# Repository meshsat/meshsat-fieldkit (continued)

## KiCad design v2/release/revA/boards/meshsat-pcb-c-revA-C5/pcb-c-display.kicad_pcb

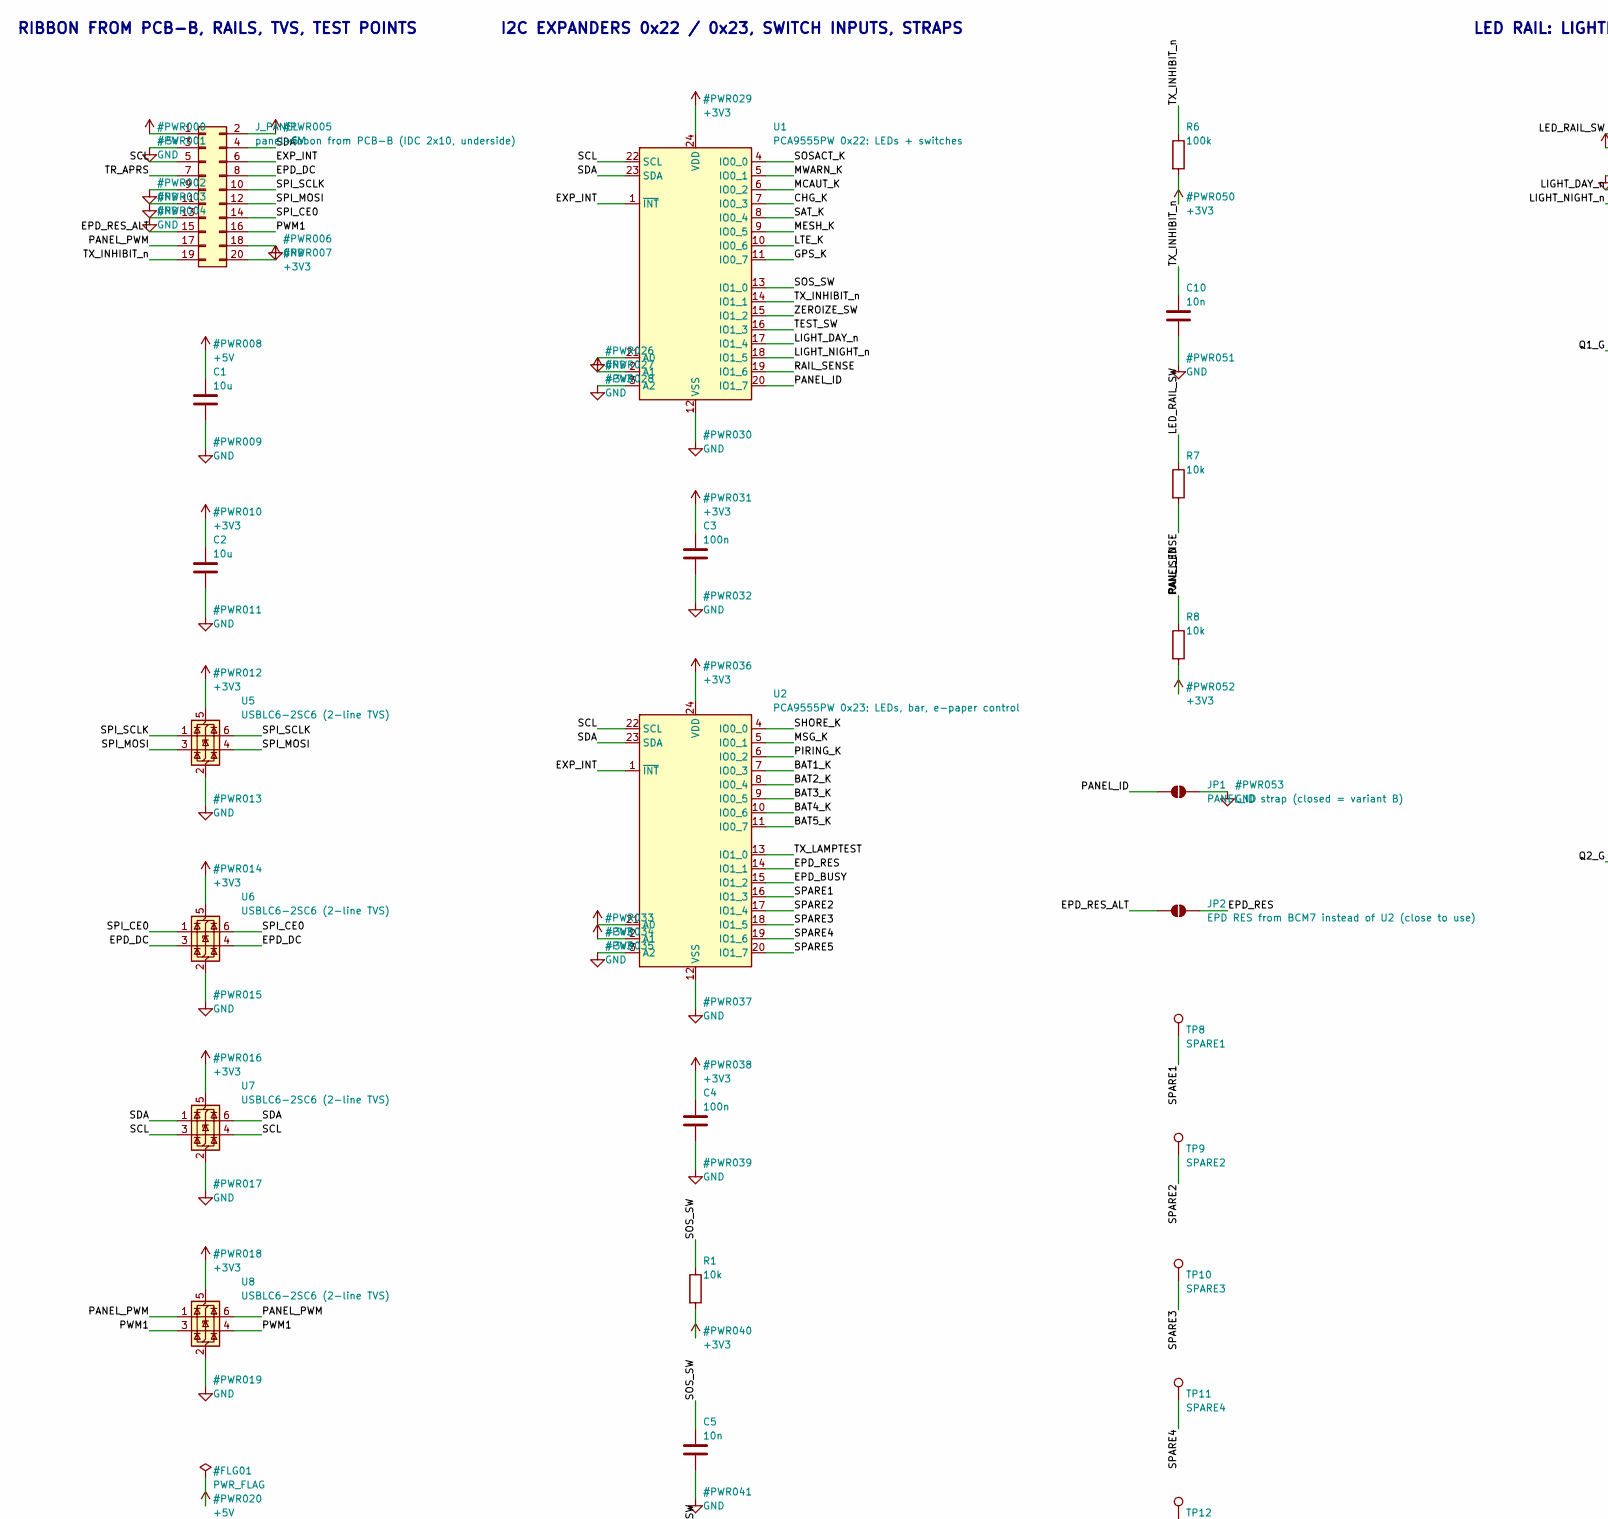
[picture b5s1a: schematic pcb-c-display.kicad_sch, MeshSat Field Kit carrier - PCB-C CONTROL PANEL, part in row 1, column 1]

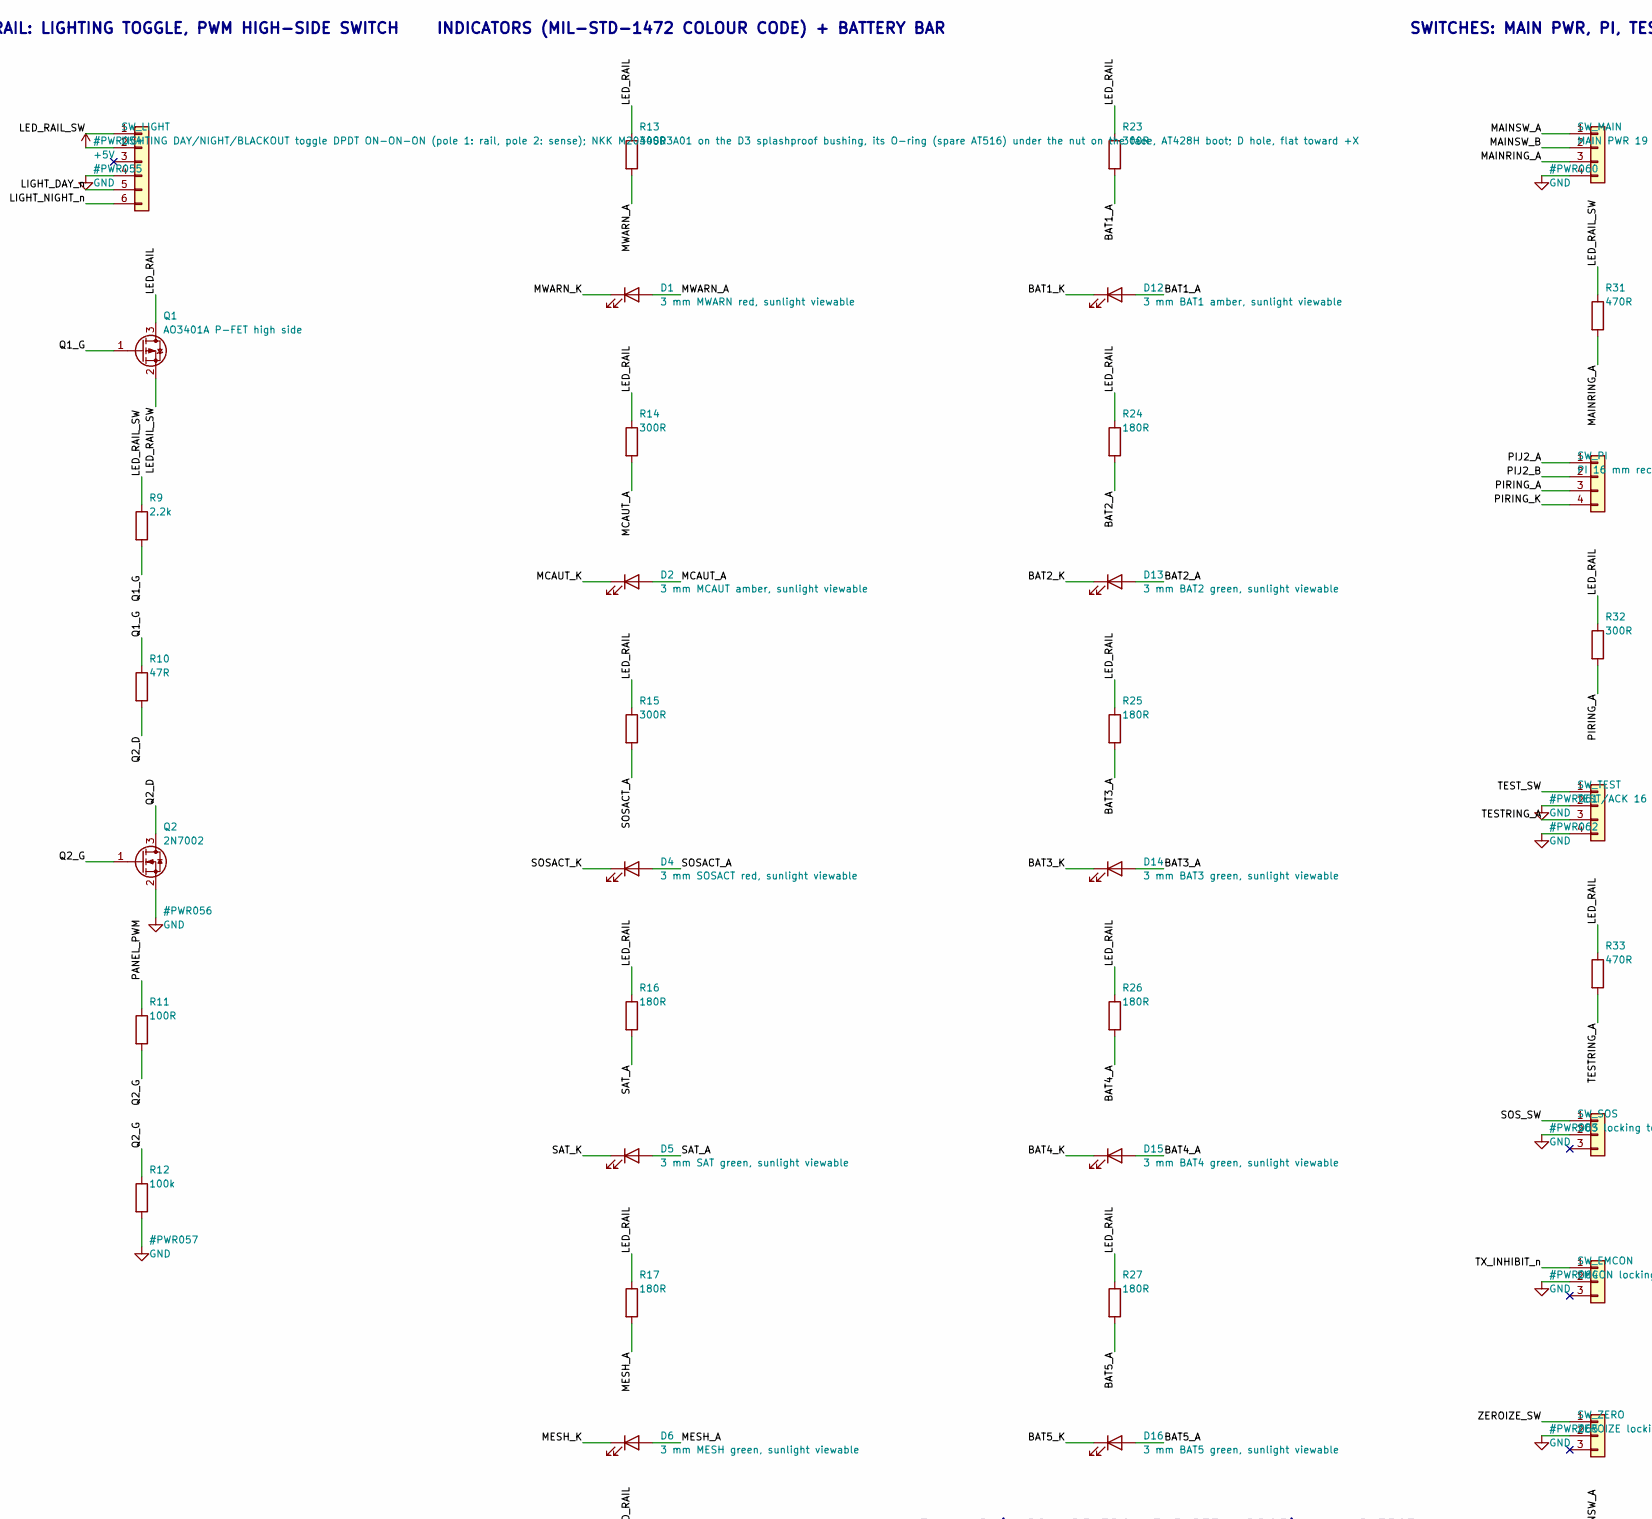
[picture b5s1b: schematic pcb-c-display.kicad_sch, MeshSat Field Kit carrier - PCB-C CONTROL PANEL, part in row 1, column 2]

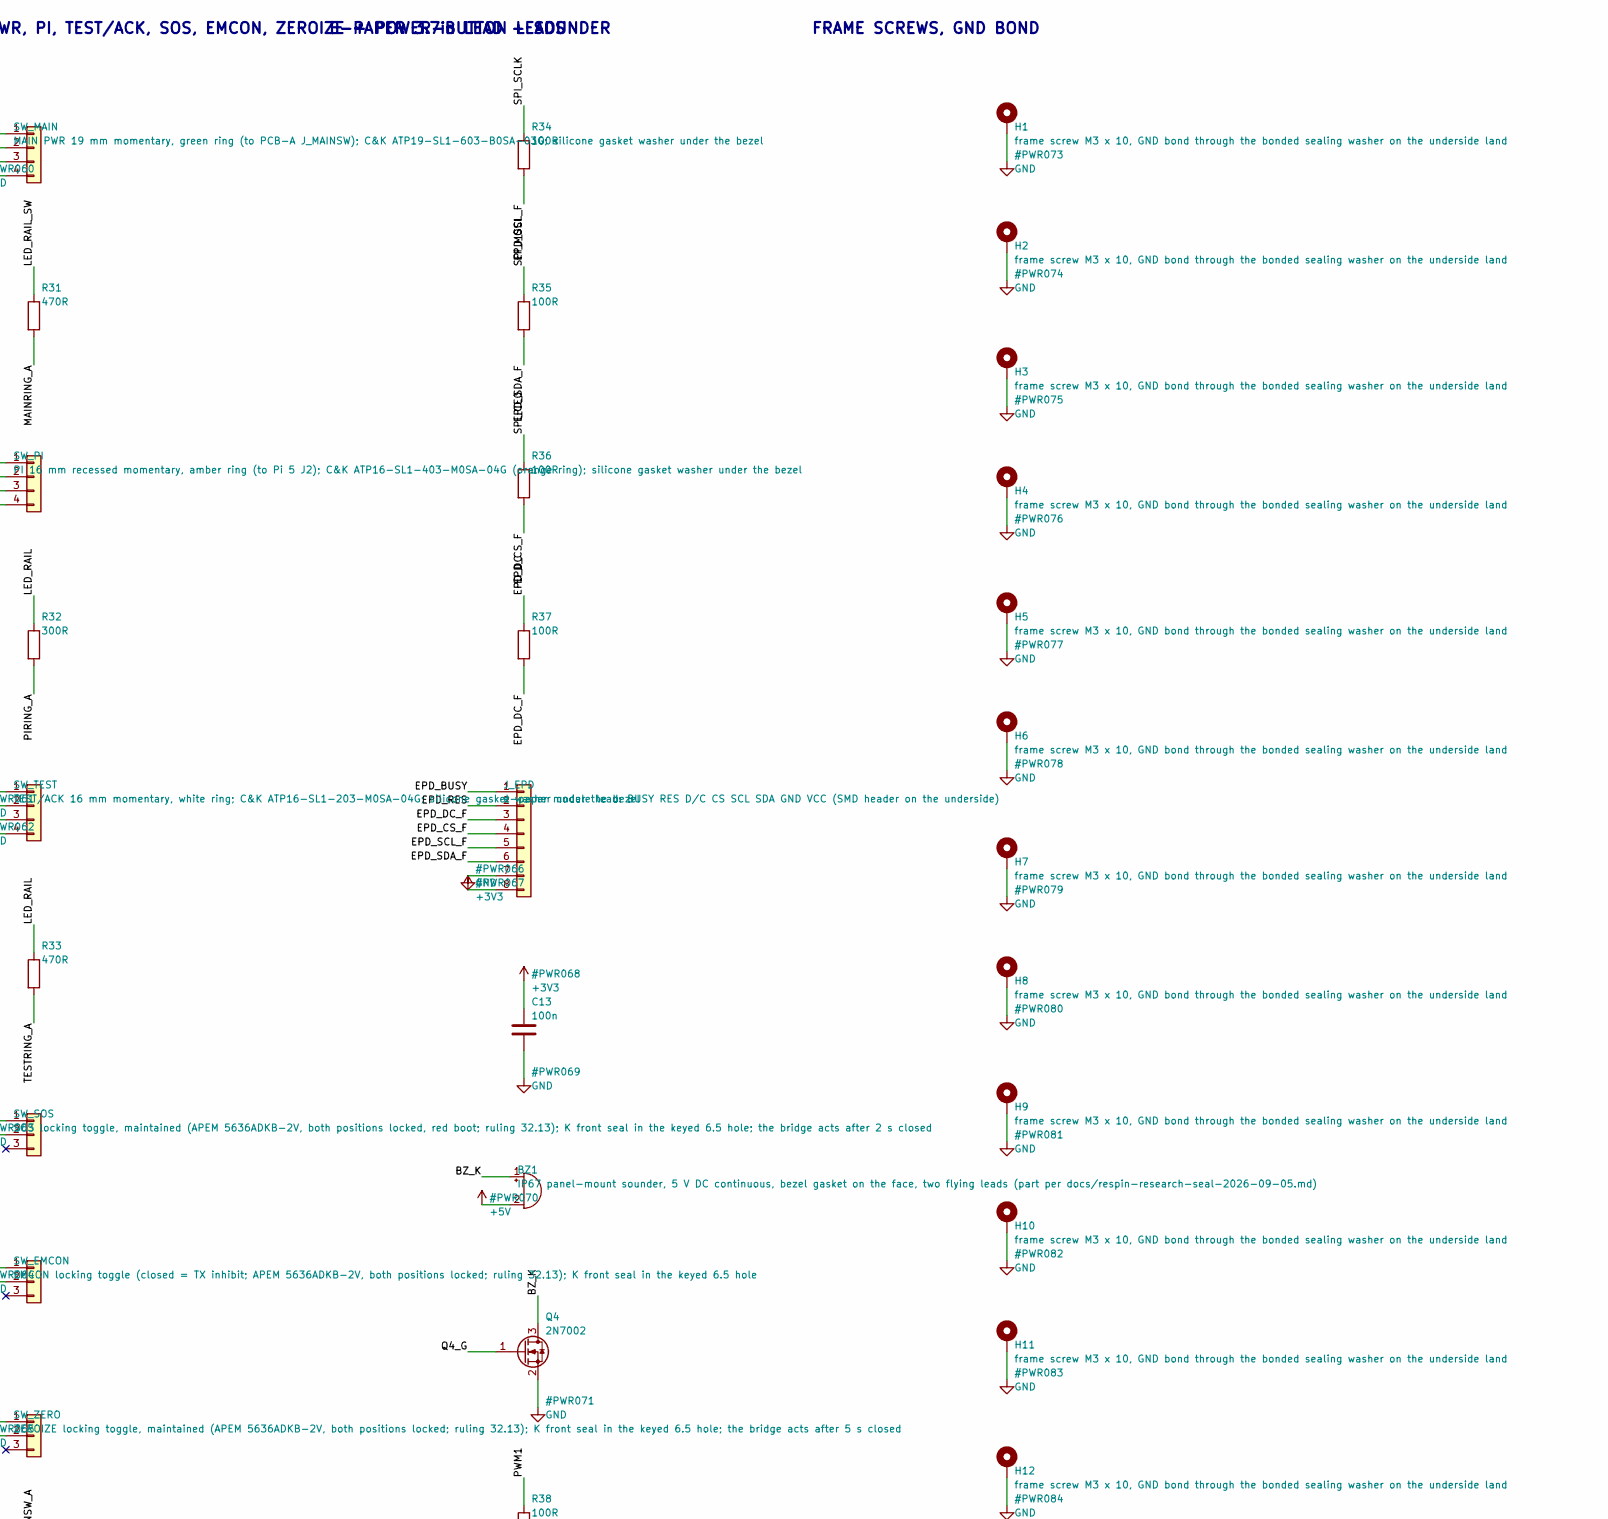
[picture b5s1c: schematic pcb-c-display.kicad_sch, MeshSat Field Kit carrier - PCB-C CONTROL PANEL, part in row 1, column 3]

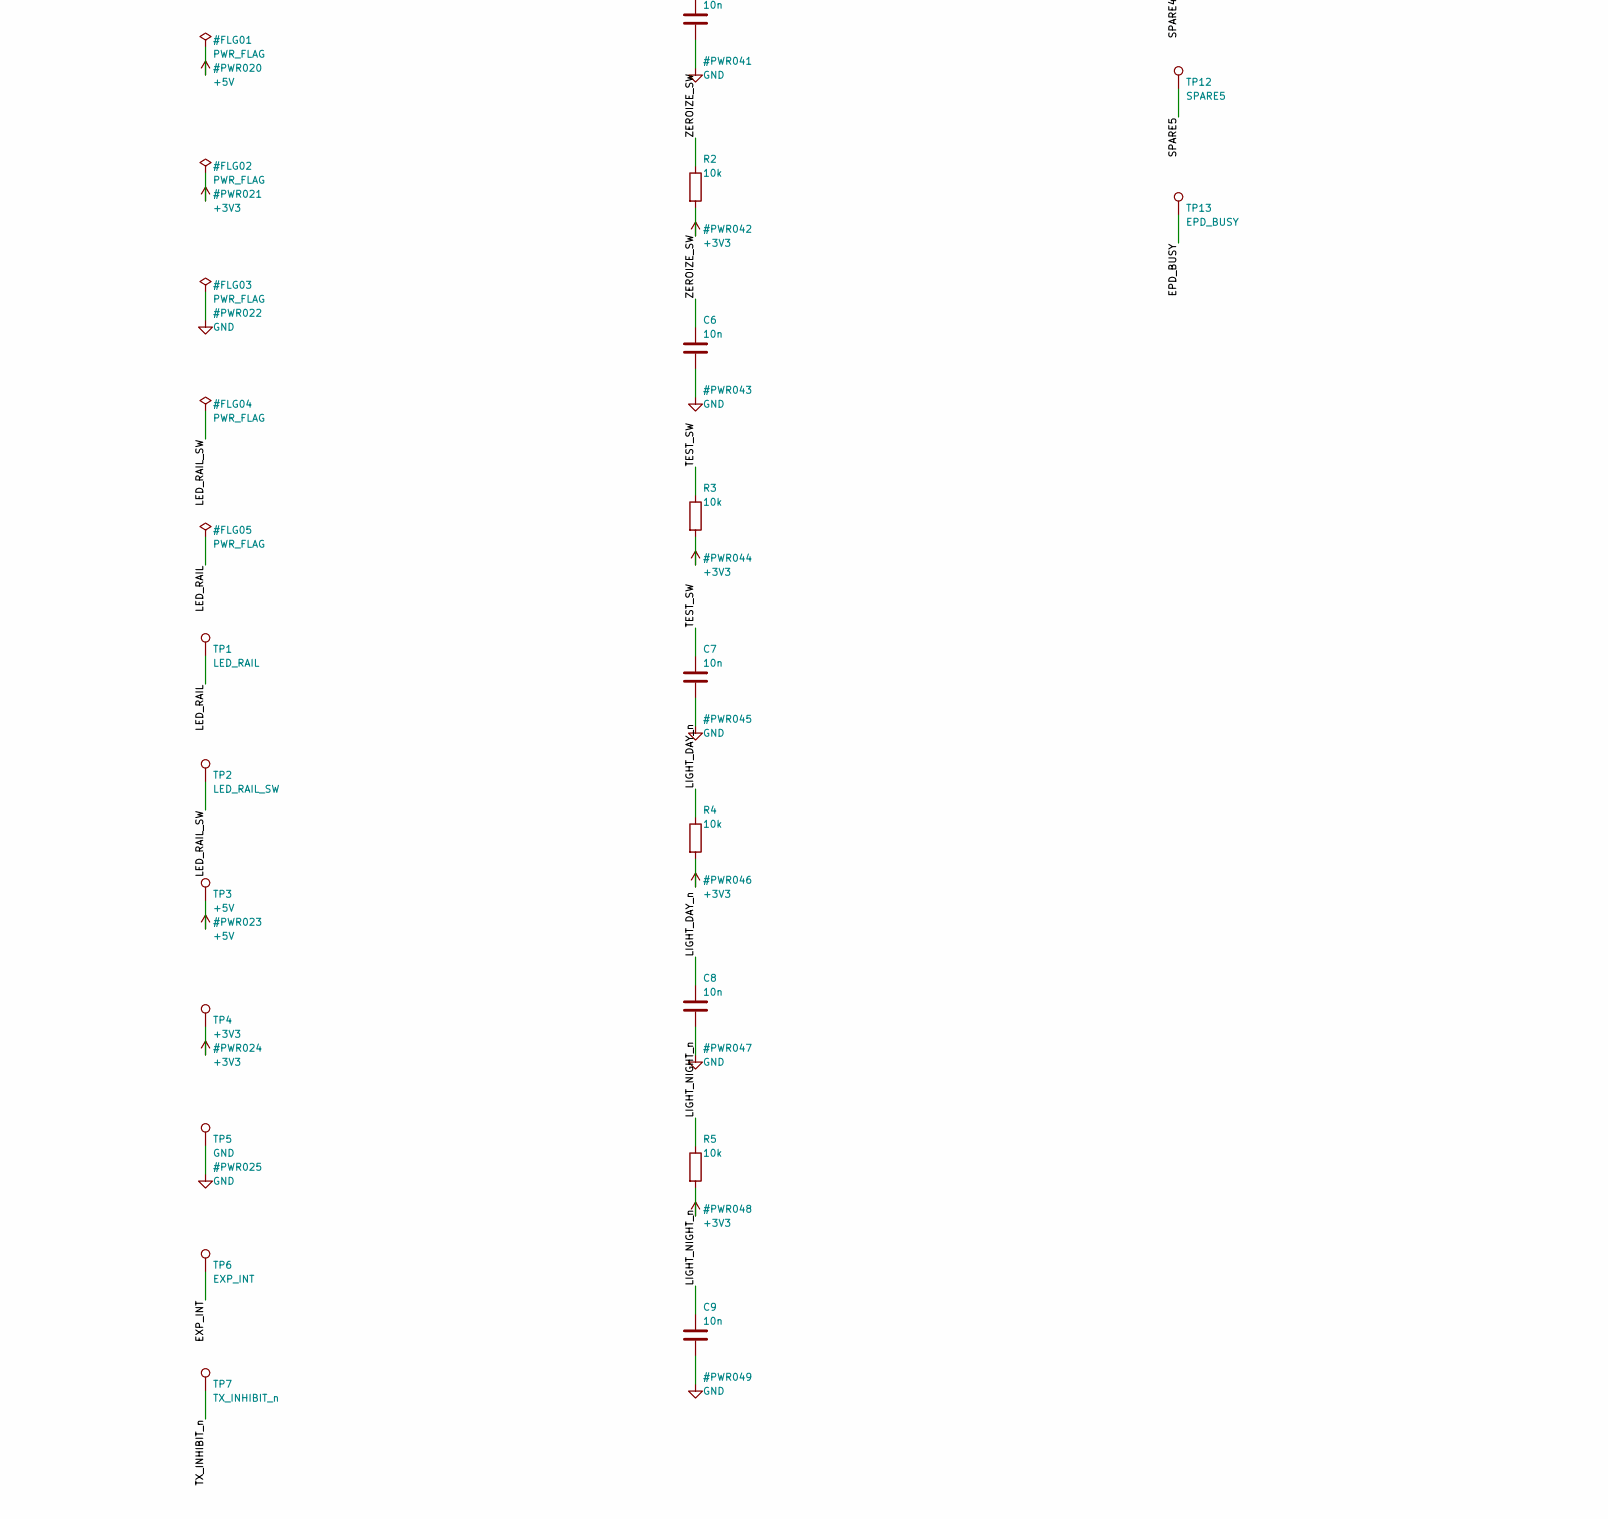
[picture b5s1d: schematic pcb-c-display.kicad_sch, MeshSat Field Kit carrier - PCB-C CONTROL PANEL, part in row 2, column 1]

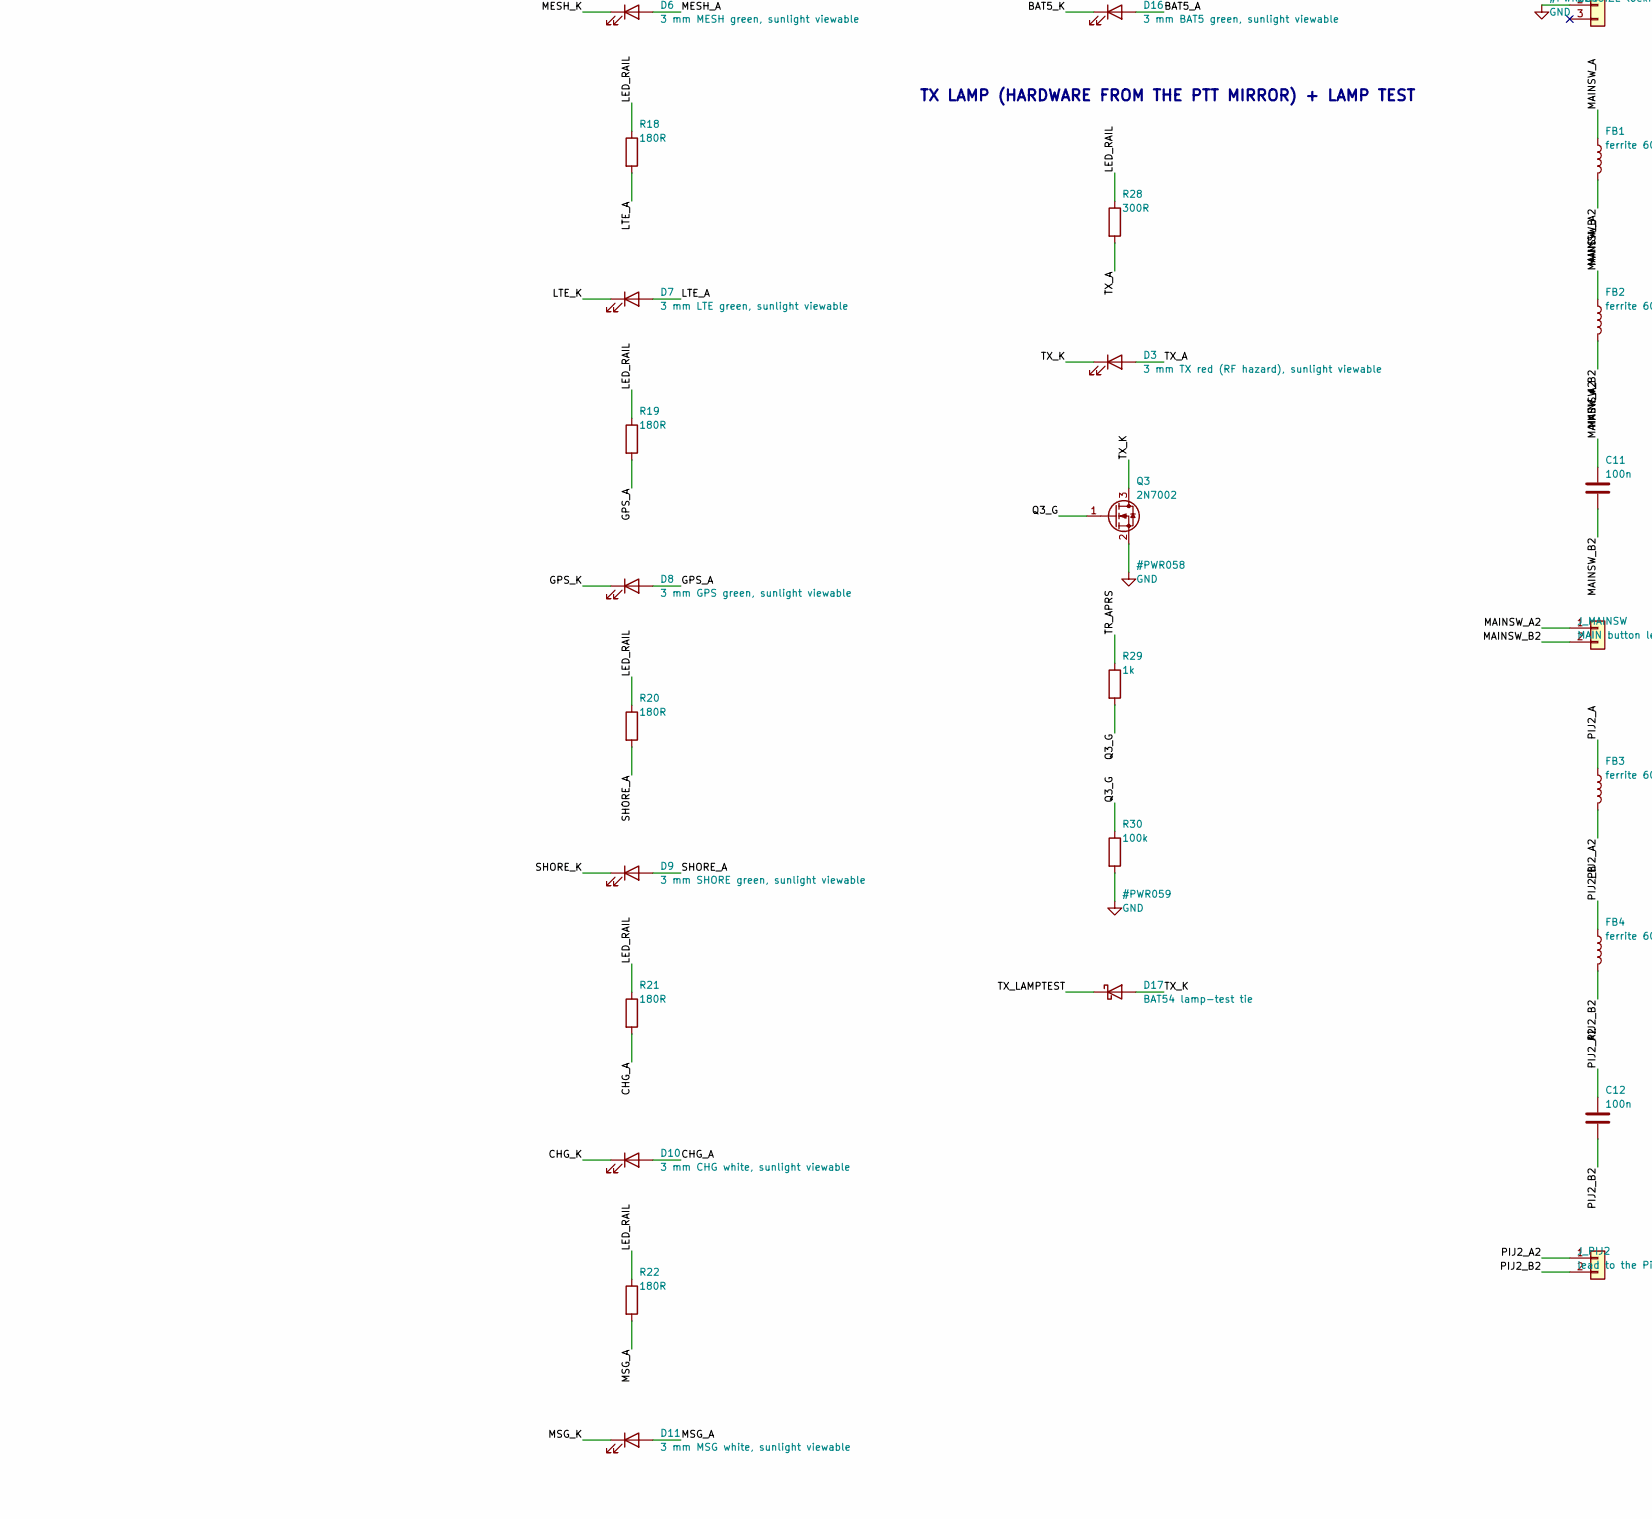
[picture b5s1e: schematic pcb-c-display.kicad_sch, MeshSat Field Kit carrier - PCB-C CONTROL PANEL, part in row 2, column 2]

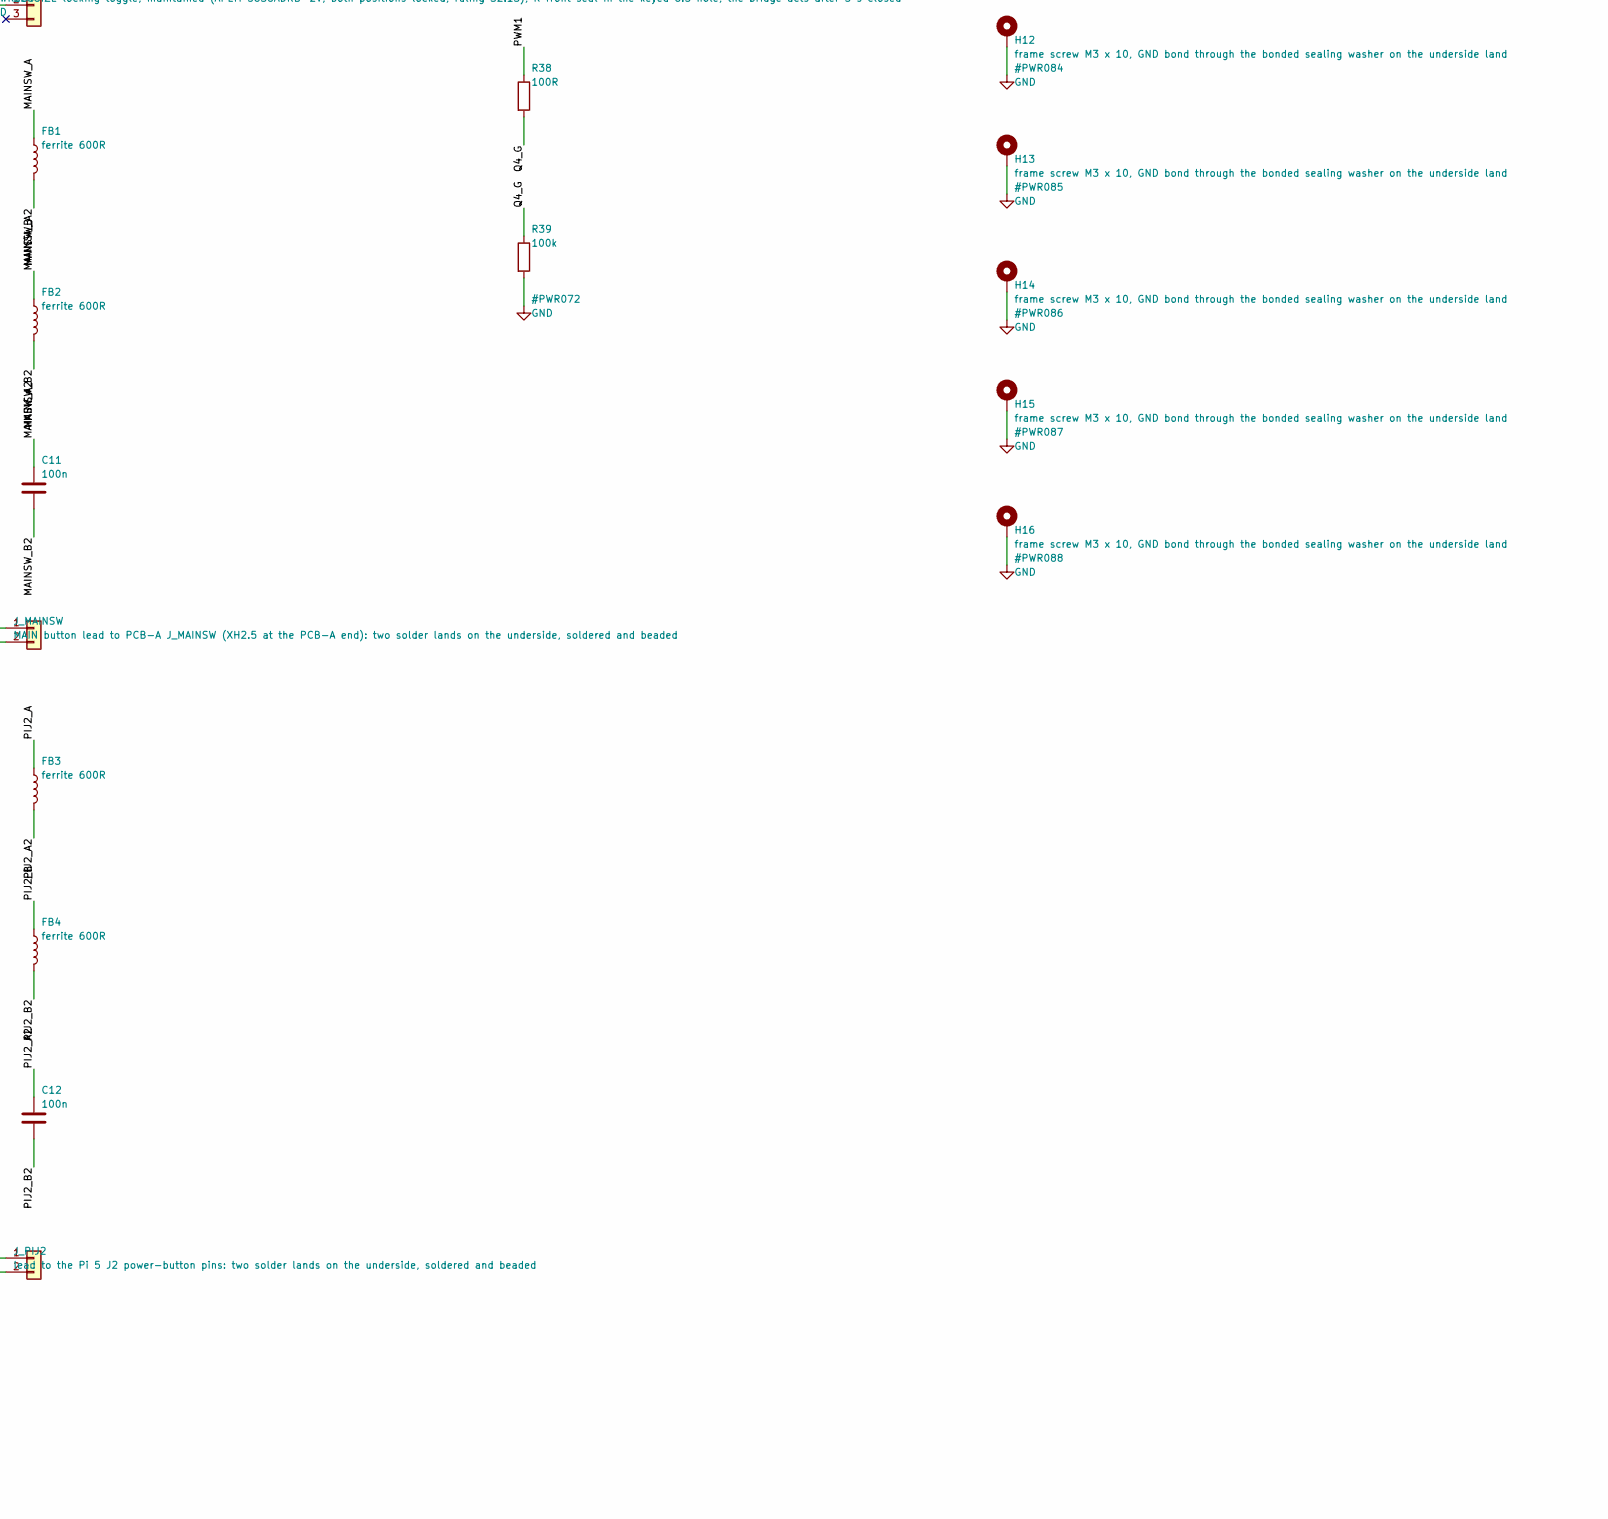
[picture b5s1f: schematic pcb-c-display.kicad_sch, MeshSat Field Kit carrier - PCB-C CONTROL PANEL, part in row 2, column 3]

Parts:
BZ1: IP67 panel-mount sounder, 5 V DC continuous, beze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; PanelSounder
C1, C2: 10u; C_0805_2012Metric; LCSC C15850
C3, C4, C11, C12, C13: 100n; C_0603_1608Metric; LCSC C14663
C5, C6, C7, C8, C9, C10: 10n; C_0603_1608Metric; LCSC C57112
D1: 3 mm MWARN red, sunlight viewable; LED_D3.0mm
D2: 3 mm MCAUT amber, sunlight viewable; LED_D3.0mm
D3: 3 mm TX red (RF hazard), sunlight viewable; LED_D3.0mm
D4: 3 mm SOSACT red, sunlight viewable; LED_D3.0mm
D5: 3 mm SAT green, sunlight viewable; LED_D3.0mm
D6: 3 mm MESH green, sunlight viewable; LED_D3.0mm
D7: 3 mm LTE green, sunlight viewable; LED_D3.0mm
D8: 3 mm GPS green, sunlight viewable; LED_D3.0mm
D9: 3 mm SHORE green, sunlight viewable; LED_D3.0mm
D10: 3 mm CHG white, sunlight viewable; LED_D3.0mm
D11: 3 mm MSG white, sunlight viewable; LED_D3.0mm
D12: 3 mm BAT1 amber, sunlight viewable; LED_D3.0mm
D13: 3 mm BAT2 green, sunlight viewable; LED_D3.0mm
D14: 3 mm BAT3 green, sunlight viewable; LED_D3.0mm
D15: 3 mm BAT4 green, sunlight viewable; LED_D3.0mm
D16: 3 mm BAT5 green, sunlight viewable; LED_D3.0mm
D17: BAT54 lamp-test tie; D_SOD-123; LCSC C2166
FB1, FB2, FB3, FB4: ferrite 600R; L_0603_1608Metric; LCSC C1017
H1, H2, H3, H4, H5, H6, H7, H8, H9, H10, H11, H12, H13, H14, H15, H16: frame screw M3 x 10, GND bond through the bonded 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; FrameScrew_M3_GND
JP1: PANEL_ID strap (closed = variant B); SolderJumper-2_P1.3mm_Open_RoundedPad1.0x1.5mm
JP2: EPD RES from BCM7 instead of U2 (close to use); SolderJumper-2_P1.3mm_Open_RoundedPad1.0x1.5mm
J_EPD: e-paper module lead: BUSY RES D/C CS SCL SDA GND 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; PinHeader_1x08_P2.54mm_Vertical_SMD_Pin1Left
J_MAINSW: MAIN button lead to PCB-A J_MAINSW (XH2.5 at the 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; LeadLands_1x02
J_PANEL: panel ribbon from PCB-B (IDC 2x10, underside); IDC-Header_2x10_P2.54mm_Vertical_SMD
J_PIJ2: lead to the Pi 5 J2 power-button pins: two solder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; LeadLands_1x02
Q1: AO3401A P-FET high side; SOT-23; LCSC C15127
Q2, Q3, Q4: 2N7002; SOT-23; LCSC C8545
R1, R2, R3, R4, R5, R7, R8: 10k; R_0603_1608Metric; LCSC C25804
R6, R12, R30, R39: 100k; R_0603_1608Metric; LCSC C25803
R9: 2.2k; R_0603_1608Metric; LCSC C4190
R10: 47R; R_0603_1608Metric; LCSC C25118
R11, R34, R35, R36, R37, R38: 100R; R_0603_1608Metric; LCSC C22775
R13, R14, R15, R23, R28, R32: 300R; R_0603_1608Metric; LCSC C23025
R16, R17, R18, R19, R20, R21, R22, R24, R25, R26, R27: 180R; R_0603_1608Metric; LCSC C25270
R29: 1k; R_0603_1608Metric; LCSC C11702
R31, R33: 470R; R_0603_1608Metric; LCSC C23179
SW_EMCON: EMCON locking toggle (closed = TX inhibit; APEM 5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; GuardedToggle_SPDT
SW_LIGHT: LIGHTING DAY/NIGHT/BLACKOUT toggle DPDT ON-ON-ON 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; PanelToggle_DPDT
SW_MAIN: MAIN PWR 19 mm momentary, green ring (to PCB-A J_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; PanelSwitch_19mm
SW_PI: PI 16 mm recessed momentary, amber ring (to Pi 5 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; PanelSwitch_16mm
SW_SOS: SOS locking toggle, maintained (APEM 5636ADKB-2V,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; GuardedToggle_SPDT
SW_TEST: TEST/ACK 16 mm momentary, white ring; C&K ATP16-S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; PanelSwitch_16mm
SW_ZERO: ZEROIZE locking toggle, maintained (APEM 5636ADKB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; GuardedToggle_SPDT
TP1: LED_RAIL; TestPoint_Pad_D1.5mm
TP2: LED_RAIL_SW; TestPoint_Pad_D1.5mm
TP3: +5V; TestPoint_Pad_D1.5mm
TP4: +3V3; TestPoint_Pad_D1.5mm
TP5: GND; TestPoint_Pad_D1.5mm
TP6: EXP_INT; TestPoint_Pad_D1.5mm
TP7: TX_INHIBIT_n; TestPoint_Pad_D1.5mm
TP8: SPARE1; TestPoint_Pad_D1.5mm
TP9: SPARE2; TestPoint_Pad_D1.5mm
TP10: SPARE3; TestPoint_Pad_D1.5mm
TP11: SPARE4; TestPoint_Pad_D1.5mm
TP12: SPARE5; TestPoint_Pad_D1.5mm
TP13: EPD_BUSY; TestPoint_Pad_D1.5mm
U1: PCA9555PW 0x22: LEDs + switches; TSSOP-24_4.4x7.8mm_P0.65mm; LCSC C50993
U2: PCA9555PW 0x23: LEDs, bar, e-paper control; TSSOP-24_4.4x7.8mm_P0.65mm; LCSC C50993
U5, U6, U7, U8: USBLC6-2SC6 (2-line TVS); SOT-23-6; LCSC C7519

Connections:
+3V3: C2.1, C3.1, C4.1, C13.1, J_EPD.8, J_PANEL.20, R1.2, R2.2, R3.2, R4.2, R5.2, R6.2, R8.2, TP4.1, U1.2 (A1), U1.24 (VDD), U2.2 (A1), U2.21 (A0), U2.24 (VDD), U5.5 (VBUS), U6.5 (VBUS), U7.5 (VBUS), U8.5 (VBUS)
+5V: BZ1.2 (-), C1.1, J_PANEL.1, J_PANEL.2, SW_LIGHT.2, TP3.1
/BAT1_A: D12.2 (A), R23.2
/BAT1_K: D12.1 (K), U2.7 (IO0_3)
/BAT2_A: D13.2 (A), R24.2
/BAT2_K: D13.1 (K), U2.8 (IO0_4)
/BAT3_A: D14.2 (A), R25.2
/BAT3_K: D14.1 (K), U2.9 (IO0_5)
/BAT4_A: D15.2 (A), R26.2
/BAT4_K: D15.1 (K), U2.10 (IO0_6)
/BAT5_A: D16.2 (A), R27.2
/BAT5_K: D16.1 (K), U2.11 (IO0_7)
/BZ_K: BZ1.1 (+), Q4.3 (D)
/CHG_A: D10.2 (A), R21.2
/CHG_K: D10.1 (K), U1.7 (IO0_3)
/EPD_BUSY: J_EPD.1, TP13.1, U2.15 (IO1_2)
/EPD_CS_F: J_EPD.4, R36.2
/EPD_DC: J_PANEL.8, R37.1, U6.3 (I/O2), U6.4 (I/O2)
/EPD_DC_F: J_EPD.3, R37.2
/EPD_RES: JP2.2 (B), J_EPD.2, U2.14 (IO1_1)
/EPD_RES_ALT: JP2.1 (A), J_PANEL.15
/EPD_SCL_F: J_EPD.5, R34.2
/EPD_SDA_F: J_EPD.6, R35.2
/EXP_INT: J_PANEL.6, TP6.1, U1.1 (~INT), U2.1 (~INT)
/GPS_A: D8.2 (A), R19.2
/GPS_K: D8.1 (K), U1.11 (IO0_7)
/LED_RAIL: Q1.3 (D), R13.1, R14.1, R15.1, R16.1, R17.1, R18.1, R19.1, R20.1, R21.1, R22.1, R23.1, R24.1, R25.1, R26.1, R27.1, R28.1, R32.1, R33.1, TP1.1
/LED_RAIL_SW: Q1.2 (S), R7.1, R9.1, R31.1, SW_LIGHT.1, TP2.1
/LIGHT_DAY_n: C8.1, R4.1, SW_LIGHT.5, U1.17 (IO1_4)
/LIGHT_NIGHT_n: C9.1, R5.1, SW_LIGHT.6, U1.18 (IO1_5)
/LTE_A: D7.2 (A), R18.2
/LTE_K: D7.1 (K), U1.10 (IO0_6)
/MAINRING_A: R31.2, SW_MAIN.3
/MAINSW_A: FB1.1, SW_MAIN.1
/MAINSW_A2: C11.1, FB1.2, J_MAINSW.1
/MAINSW_B: FB2.1, SW_MAIN.2
/MAINSW_B2: C11.2, FB2.2, J_MAINSW.2
/MCAUT_A: D2.2 (A), R14.2
/MCAUT_K: D2.1 (K), U1.6 (IO0_2)
/MESH_A: D6.2 (A), R17.2
/MESH_K: D6.1 (K), U1.9 (IO0_5)
/MSG_A: D11.2 (A), R22.2
/MSG_K: D11.1 (K), U2.5 (IO0_1)
/MWARN_A: D1.2 (A), R13.2
/MWARN_K: D1.1 (K), U1.5 (IO0_1)
/PANEL_ID: JP1.1 (A), R8.1, U1.20 (IO1_7)
/PANEL_PWM: J_PANEL.17, R11.1, U8.1 (I/O1), U8.6 (I/O1)
/PIJ2_A: FB3.1, SW_PI.1
/PIJ2_A2: C12.1, FB3.2, J_PIJ2.1
/PIJ2_B: FB4.1, SW_PI.2
/PIJ2_B2: C12.2, FB4.2, J_PIJ2.2
/PIRING_A: R32.2, SW_PI.3
/PIRING_K: SW_PI.4, U2.6 (IO0_2)
/PWM1: J_PANEL.16, R38.1, U8.3 (I/O2), U8.4 (I/O2)
/Q1_G: Q1.1 (G), R9.2, R10.1
/Q2_D: Q2.3 (D), R10.2
/Q2_G: Q2.1 (G), R11.2, R12.1
/Q3_G: Q3.1 (G), R29.2, R30.1
/Q4_G: Q4.1 (G), R38.2, R39.1
/RAIL_SENSE: R7.2, U1.19 (IO1_6)
/SAT_A: D5.2 (A), R16.2
/SAT_K: D5.1 (K), U1.8 (IO0_4)
/SCL: J_PANEL.5, U1.22 (SCL), U2.22 (SCL), U7.3 (I/O2), U7.4 (I/O2)
/SDA: J_PANEL.4, U1.23 (SDA), U2.23 (SDA), U7.1 (I/O1), U7.6 (I/O1)
/SHORE_A: D9.2 (A), R20.2
/SHORE_K: D9.1 (K), U2.4 (IO0_0)
/SOSACT_A: D4.2 (A), R15.2
/SOSACT_K: D4.1 (K), U1.4 (IO0_0)
/SOS_SW: C5.1, R1.1, SW_SOS.1, U1.13 (IO1_0)
/SPARE1: TP8.1, U2.16 (IO1_3)
/SPARE2: TP9.1, U2.17 (IO1_4)
/SPARE3: TP10.1, U2.18 (IO1_5)
/SPARE4: TP11.1, U2.19 (IO1_6)
/SPARE5: TP12.1, U2.20 (IO1_7)
/SPI_CE0: J_PANEL.14, R36.1, U6.1 (I/O1), U6.6 (I/O1)
/SPI_MOSI: J_PANEL.12, R35.1, U5.3 (I/O2), U5.4 (I/O2)
/SPI_SCLK: J_PANEL.10, R34.1, U5.1 (I/O1), U5.6 (I/O1)
/TESTRING_A: R33.2, SW_TEST.3
/TEST_SW: C7.1, R3.1, SW_TEST.1, U1.16 (IO1_3)
/TR_APRS: J_PANEL.7, R29.1
/TX_A: D3.2 (A), R28.2
/TX_INHIBIT_n: C10.1, J_PANEL.19, R6.1, SW_EMCON.1, TP7.1, U1.14 (IO1_1)
/TX_K: D3.1 (K), D17.2 (A), Q3.3 (D)
/TX_LAMPTEST: D17.1 (K), U2.13 (IO1_0)
/ZEROIZE_SW: C6.1, R2.1, SW_ZERO.1, U1.15 (IO1_2)
GND: C1.2, C2.2, C3.2, C4.2, C5.2, C6.2, C7.2, C8.2, C9.2, C10.2, C13.2, H1.1, H2.1, H3.1, H4.1, H5.1, H6.1, H7.1, H8.1, H9.1, H10.1, H11.1, H12.1, H13.1, H14.1, H15.1, H16.1, JP1.2 (B), J_EPD.7, J_PANEL.3, J_PANEL.9, J_PANEL.11, J_PANEL.13, J_PANEL.18, Q2.2 (S), Q3.2 (S), Q4.2 (S), R12.2, R30.2, R39.2, SW_EMCON.2, SW_LIGHT.4, SW_MAIN.4, SW_SOS.2, SW_TEST.2, SW_TEST.4, SW_ZERO.2, TP5.1, U1.3 (A2), U1.12 (VSS), U1.21 (A0), U2.3 (A2), U2.12 (VSS), U5.2 (GND), U6.2 (GND), U7.2 (GND), U8.2 (GND)

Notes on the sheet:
RIBBON FROM PCB-B, RAILS, TVS, TEST POINTS
I2C EXPANDERS 0x22 / 0x23, SWITCH INPUTS, STRAPS
LED RAIL: LIGHTING TOGGLE, PWM HIGH-SIDE SWITCH
INDICATORS (MIL-STD-1472 COLOUR CODE) + BATTERY BAR
TX LAMP (HARDWARE FROM THE PTT MIRROR) + LAMP TEST
SWITCHES: MAIN PWR, PI, TEST/ACK, SOS, EMCON, ZEROIZE + POWER-BUTTON LEADS
E-PAPER 3.7in LEAD + SOUNDER
FRAME SCREWS, GND BOND

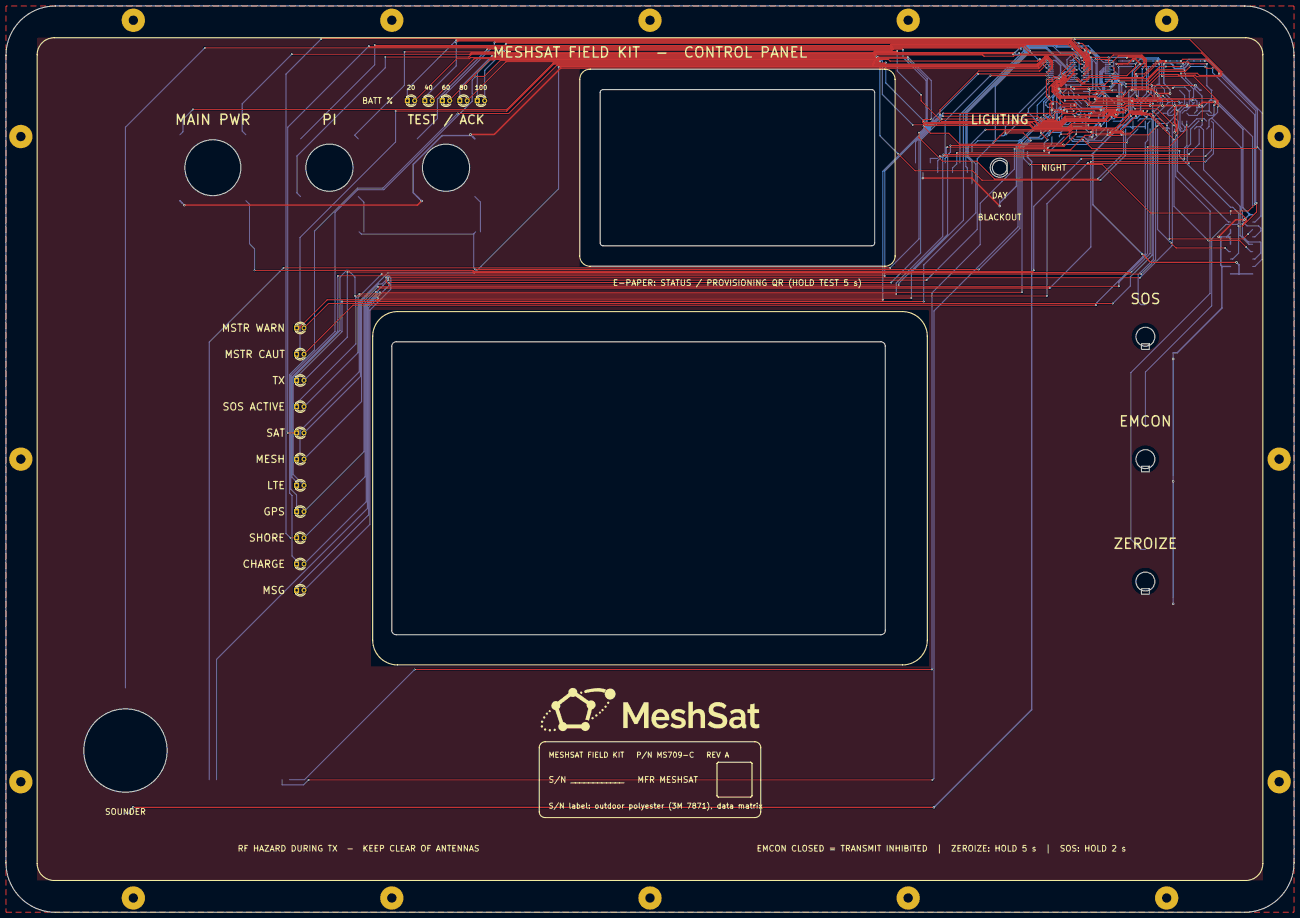
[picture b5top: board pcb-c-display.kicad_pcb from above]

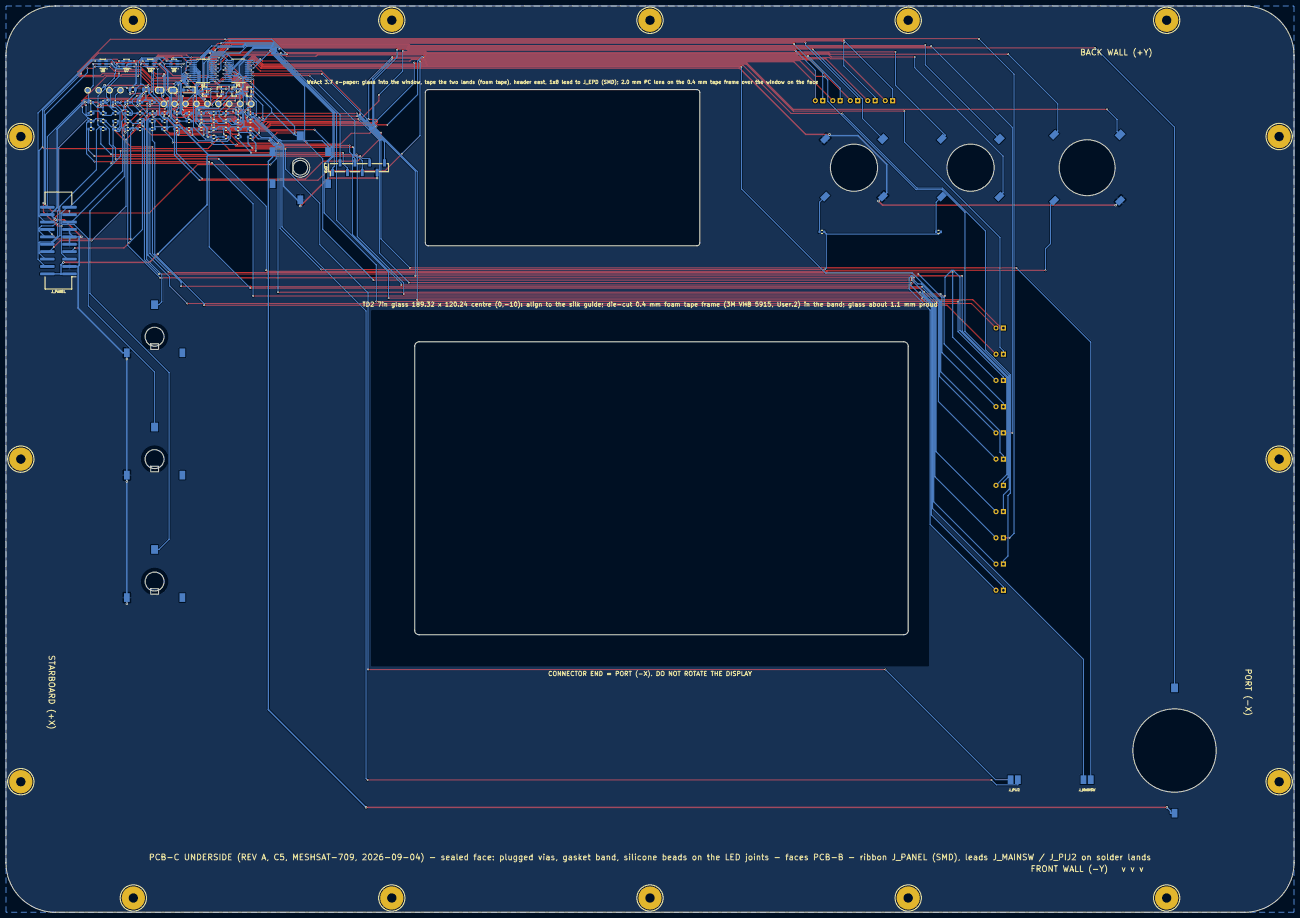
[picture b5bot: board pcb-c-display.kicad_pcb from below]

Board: 2 copper layers, 442.0 x 311.0 mm, 126 parts (86 on the bottom side), 86 nets.
